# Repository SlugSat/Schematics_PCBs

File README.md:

# Schematics_PCBs
PCB Schematics for the whole team

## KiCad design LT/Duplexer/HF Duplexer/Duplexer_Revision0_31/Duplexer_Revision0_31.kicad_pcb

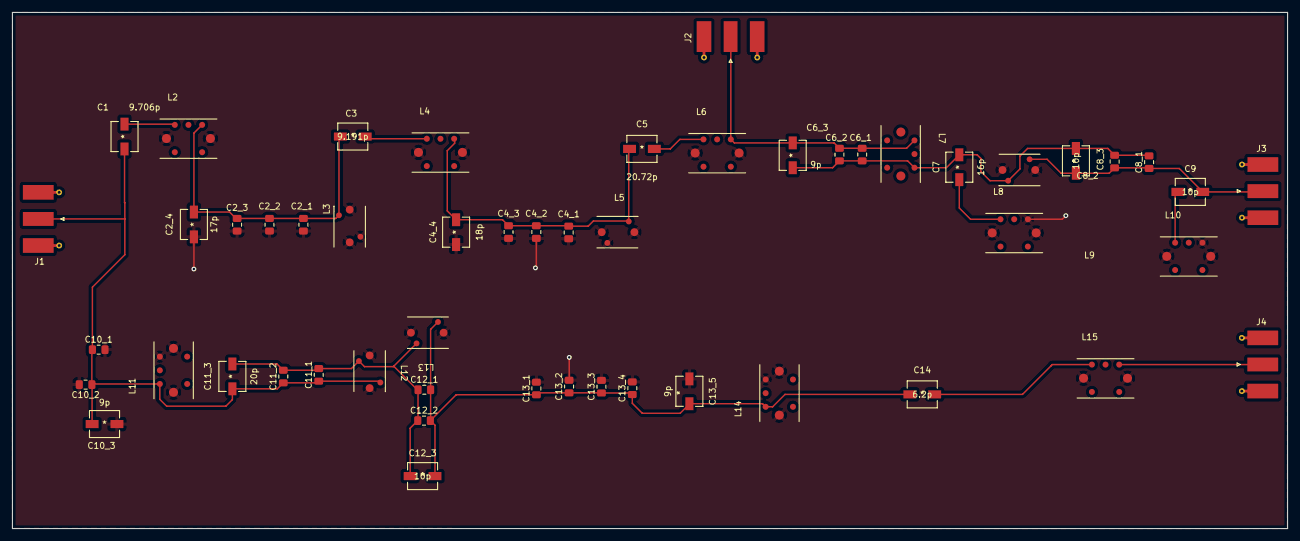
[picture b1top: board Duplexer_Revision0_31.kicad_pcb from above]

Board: 2 copper layers, 210.0 x 85.0 mm, 52 parts (0 on the bottom side), 16 nets.

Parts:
C1: 9.706p; GKG30086-05
C2_1, C13_1: 2.2n; C_0805_2012Metric_Pad1.18x1.45mm_HandSolder
C2_2, C4_2, C12_2: 100p; C_0805_2012Metric_Pad1.18x1.45mm_HandSolder
C2_3: 330p; C_0805_2012Metric_Pad1.18x1.45mm_HandSolder
C2_4: 17p; GKG30086-05
C3: 9.191p; GKG30086-05
C4_1, C10_1: 1.5n; C_0805_2012Metric_Pad1.18x1.45mm_HandSolder
C4_3, C8_1: 560p; C_0805_2012Metric_Pad1.18x1.45mm_HandSolder
C4_4: 18p; GKG30086-05
C5: 20.72p; GKG30086-05
C6_1, C13_2, C13_3: 1n; C_0805_2012Metric_Pad1.18x1.45mm_HandSolder
C6_2, C10_2, C13_4: 91p; C_0805_2012Metric_Pad1.18x1.45mm_HandSolder
C6_3, C10_3, C13_5: 9p; GKG30086-05
C7: 16p; GKG30086-05
C8_2: 180p; C_0805_2012Metric_Pad1.18x1.45mm_HandSolder
C8_3, C9, C12_3: 10p; GKG30086-05
C11_1, C12_1: 220p; C_0805_2012Metric_Pad1.18x1.45mm_HandSolder
C11_2: 30p; C_0805_2012Metric_Pad1.18x1.45mm_HandSolder
C11_3: 20p; GKG30086-05
C14: 6.2p; GKG30086-05
J1, J2, J3, J4: SMA_H_CONNECTOR; SMA_Molex_73251-1153_EdgeMount_Horizontal
L2: 5.827uH; 7M3_Shielded_Inductor_Series
L3: 22.44nH; 164_Shielded_Inductor_Series
L4: 6.2uH; 7M3_Shielded_Inductor_Series
L5: 26.73nH; 164_Shielded_Inductor_Series
L6: 2.895uH; 7M3_Shielded_Inductor_Series
L7: 27uH; 7M3_Shielded_Inductor_Series
L8: 1.8uH; 7M3_Shielded_Inductor_Series
L9: 39nH; 164_Shielded_Inductor_Series
L10: 3uH; 7M3_Shielded_Inductor_Series
L11: 18nH; 7M3_Shielded_Inductor_Series
L12: 91nH; 164_Shielded_Inductor_Series
L13: 110nH; 164_Shielded_Inductor_Series
L14: 6.8nH; 7M3_Shielded_Inductor_Series
L15: 4.7uH; 7M3_Shielded_Inductor_Series

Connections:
GND: C2_1.1, C2_2.1, C2_3.1, C2_4.1, C4_1.1, C4_2.1, C4_3.1, C4_4.1, C10_1.2, C10_2.2, C10_3.1, C13_1.2, C13_2.2, C13_3.2, C13_4.2, C13_5.1, L2.7 (GND), L2.8 (GND), L3.2 (GND), L3.3 (Finish), L3.4 (GND), L4.7 (GND), L4.8 (GND), L5.2 (GND), L5.3 (Finish), L5.4 (GND), L6.7 (GND), L6.8 (GND), L8.3 (Finish), L8.7 (GND), L8.8 (GND), L9.2 (GND), L9.4 (GND), L10.3 (Finish), L10.7 (GND), L10.8 (GND), L11.3 (Finish), L11.7 (GND), L11.8 (GND), L12.2 (GND), L12.4 (GND), L13.2 (GND), L13.4 (GND), L14.3 (Finish), L14.7 (GND), L14.8 (GND), L15.7 (GND), L15.8 (GND)
unnamed: C1.1, C10_1.1, C10_2.1, C10_3.2, C11_1.1, C11_2.1, C11_3.1, J1.1, L11.1 (Start), L12.1 (Start)
unnamed: C1.2, L2.1 (Start)
unnamed: C2_1.2, C2_2.2, C2_3.2, C2_4.2, C3.1, L2.3 (Finish), L3.1 (Start)
unnamed: C3.2, L4.1 (Start)
unnamed: C4_1.2, C4_2.2, C4_3.2, C4_4.2, C5.1, L4.3 (Finish), L5.1 (Start)
unnamed: C5.2, L6.1 (Start)
unnamed: C6_1.1, C6_2.1, C6_3.2, C7.2, C8_1.2, C8_2.2, C8_3.1, L7.3 (Finish), L9.1 (Start)
unnamed: C6_1.2, C6_2.2, C6_3.1, J2.1, L6.3 (Finish), L7.1 (Start)
unnamed: C7.1, L8.1 (Start)
unnamed: C8_1.1, C8_2.1, C8_3.2, C9.2, J3.1, L9.3 (Finish)
unnamed: C9.1, L10.1 (Start)
unnamed: C11_1.2, C11_2.2, C11_3.2, C12_1.1, C12_2.1, C12_3.1, L12.3 (Finish), L13.1 (Start)
unnamed: C12_1.2, C12_2.2, C12_3.2, C13_1.1, C13_2.1, C13_3.1, C13_4.1, C13_5.2, C14.1, L13.3 (Finish), L14.1 (Start)
unnamed: C14.2, L15.1 (Start)
unnamed: J4.1, L15.3 (Finish)

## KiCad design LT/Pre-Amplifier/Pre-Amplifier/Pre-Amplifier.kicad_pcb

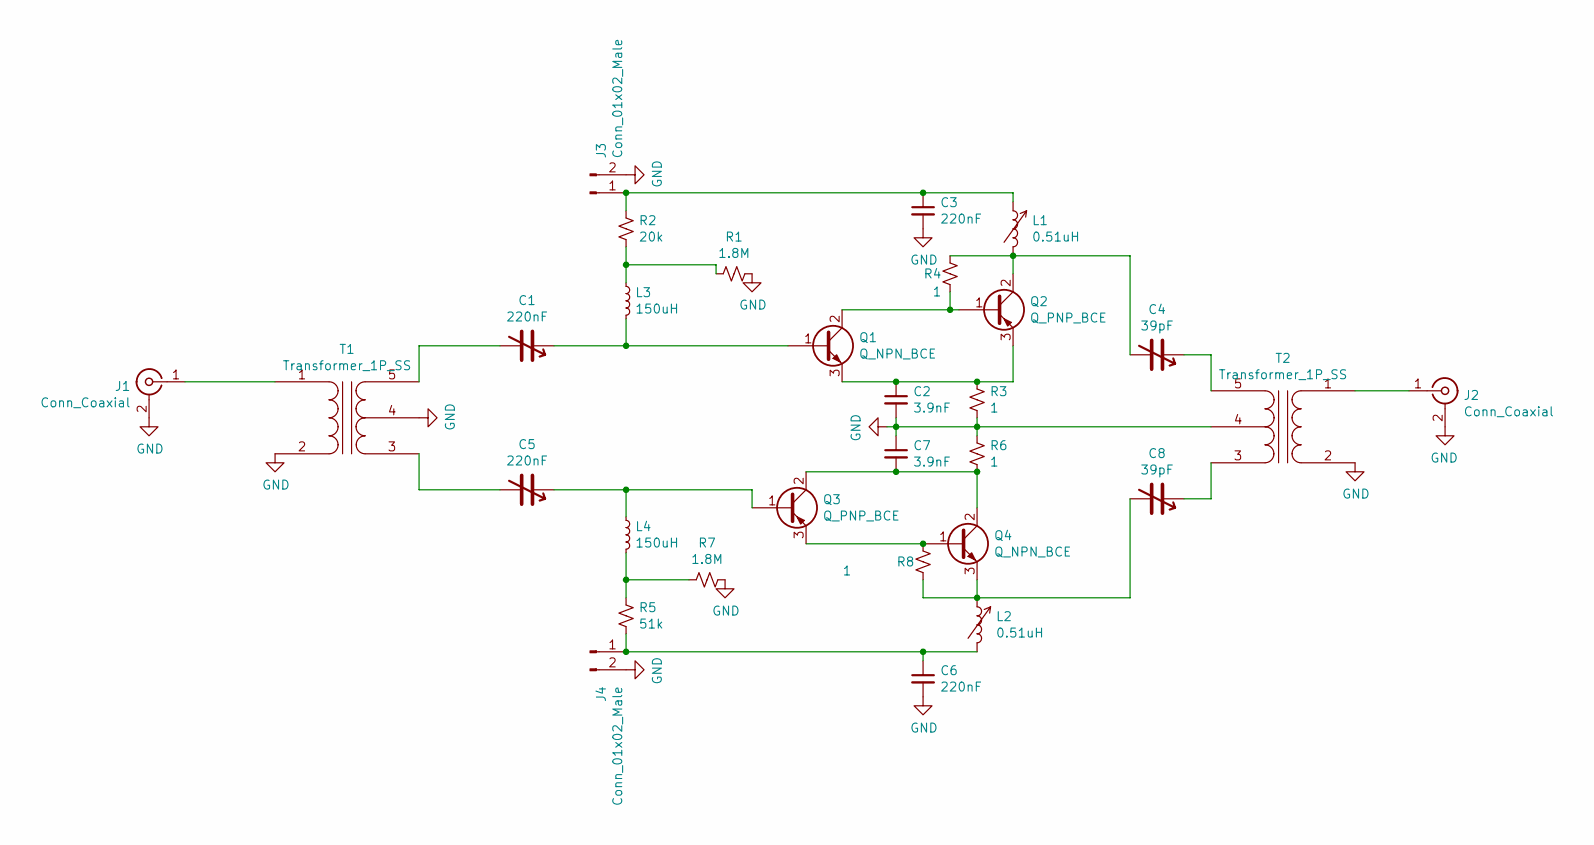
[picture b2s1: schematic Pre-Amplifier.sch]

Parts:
C1, C3, C5, C6: 220nF; C_0805_2012Metric_Pad1.18x1.45mm_HandSolder
C2, C7: 3.9nF; C_0805_2012Metric_Pad1.18x1.45mm_HandSolder
C4, C8: 39pF; C_0805_2012Metric_Pad1.18x1.45mm_HandSolder
J1, J2: Conn_Coaxial; SMA_Molex_73251-1153_EdgeMount_Horizontal
J3, J4: Conn_01x02_Male; PinHeader_1x02_P2.54mm_Vertical
L1, L2: 0.51uH; L_0805_2012Metric_Pad1.15x1.40mm_HandSolder
L3, L4: 150uH; L_0805_2012Metric_Pad1.15x1.40mm_HandSolder
Q1, Q4: Q_NPN_BCE; SOT-23_Handsoldering
Q2, Q3: Q_PNP_BCE; SOT-23_Handsoldering
R1, R7: 1.8M; R_0805_2012Metric_Pad1.20x1.40mm_HandSolder
R2: 20k; R_0805_2012Metric_Pad1.20x1.40mm_HandSolder
R3, R4, R6, R8: 1; R_0805_2012Metric_Pad1.20x1.40mm_HandSolder
R5: 51k; R_0805_2012Metric_Pad1.20x1.40mm_HandSolder
T1, T2: Transformer_1P_SS; Transformer_MACOM_SM-22

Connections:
GND: C2.2, C3.2, C6.2, C7.1, J1.2 (Ext), J2.2 (Ext), J3.2, J4.2, R1.2, R3.2, R6.1, R7.2, T1.2 (AB), T1.4 (SC), T2.2 (AB), T2.4 (SC)
unnamed: C1.1, L3.2, Q1.1 (B)
unnamed: C1.2, T1.5 (SB)
unnamed: C2.1, Q1.3 (E), Q2.3 (E), R3.1
unnamed: C3.1, J3.1, L1.1, R2.1
unnamed: C4.1, T2.5 (SB)
unnamed: C4.2, L1.2, Q2.2 (C), R4.1
unnamed: C5.1, L4.1, Q3.1 (B)
unnamed: C5.2, T1.3 (SA)
unnamed: C6.1, J4.1, L2.2, R5.2
unnamed: C7.2, Q3.2 (C), Q4.2 (C), R6.2
unnamed: C8.1, T2.3 (SA)
unnamed: C8.2, L2.1, Q4.3 (E), R8.2
unnamed: J1.1 (In), T1.1 (AA)
unnamed: J2.1 (In), T2.1 (AA)
unnamed: L3.1, R1.1, R2.2
unnamed: L4.2, R5.1, R7.1
unnamed: Q1.2 (C), Q2.1 (B), R4.2
unnamed: Q3.3 (E), Q4.1 (B), R8.1

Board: 2 copper layers, 30 parts (1 on the bottom side), 19 nets, no tracks yet.

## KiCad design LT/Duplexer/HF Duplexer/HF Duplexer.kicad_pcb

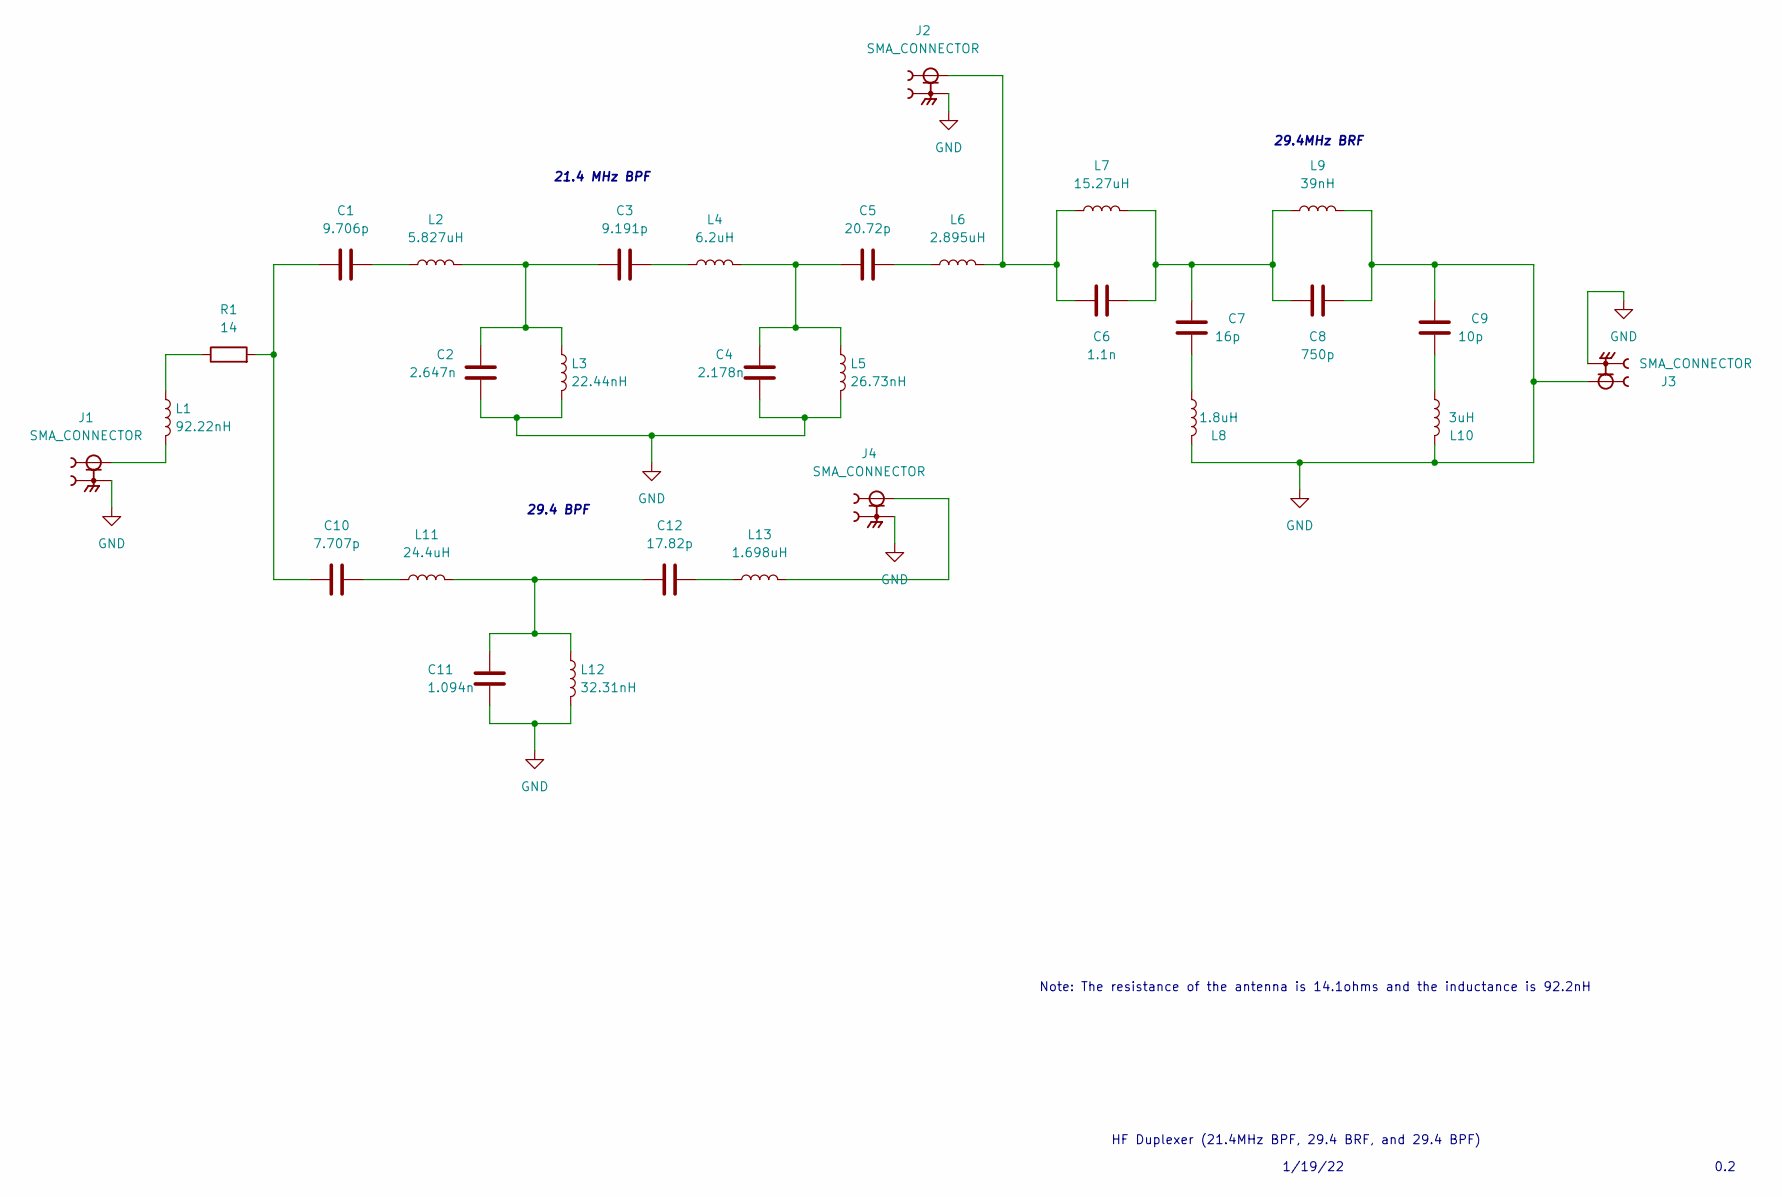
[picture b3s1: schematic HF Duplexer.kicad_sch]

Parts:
C1: 9.706p; C_0805_2012Metric_Pad1.18x1.45mm_HandSolder
C2: 2.647n; C_0805_2012Metric_Pad1.18x1.45mm_HandSolder
C3: 9.191p; C_0805_2012Metric_Pad1.18x1.45mm_HandSolder
C4: 2.178n; C_0805_2012Metric_Pad1.18x1.45mm_HandSolder
C5: 20.72p; C_0805_2012Metric_Pad1.18x1.45mm_HandSolder
C6: 1.1n; C_0805_2012Metric_Pad1.18x1.45mm_HandSolder
C7: 16p; C_0805_2012Metric_Pad1.18x1.45mm_HandSolder
C8: 750p; C_0805_2012Metric_Pad1.18x1.45mm_HandSolder
C9: 10p; C_0805_2012Metric_Pad1.18x1.45mm_HandSolder
C10: 7.707p; C_0805_2012Metric_Pad1.18x1.45mm_HandSolder
C11: 1.094n; C_0805_2012Metric_Pad1.18x1.45mm_HandSolder
C12: 17.82p; C_0805_2012Metric_Pad1.18x1.45mm_HandSolder
J1, J2, J3, J4: SMA_CONNECTOR; LPRS_SMA_CONNECTOR; PARTREV 1.3
L1: 92.22nH; L_0805_2012Metric_Pad1.15x1.40mm_HandSolder
L2: 5.827uH; L_0805_2012Metric_Pad1.15x1.40mm_HandSolder
L3: 22.44nH; L_0805_2012Metric_Pad1.15x1.40mm_HandSolder
L4: 6.2uH; L_0805_2012Metric_Pad1.15x1.40mm_HandSolder
L5: 26.73nH; L_0805_2012Metric_Pad1.15x1.40mm_HandSolder
L6: 2.895uH; L_0805_2012Metric_Pad1.15x1.40mm_HandSolder
L7: 15.27uH; L_0805_2012Metric_Pad1.15x1.40mm_HandSolder
L8: 1.8uH; L_0805_2012Metric_Pad1.15x1.40mm_HandSolder
L9: 39nH; L_0805_2012Metric_Pad1.15x1.40mm_HandSolder
L10: 3uH; L_0805_2012Metric_Pad1.15x1.40mm_HandSolder
L11: 24.4uH; L_0805_2012Metric_Pad1.15x1.40mm_HandSolder
L12: 32.31nH; L_0805_2012Metric_Pad1.15x1.40mm_HandSolder
L13: 1.698uH; L_0805_2012Metric_Pad1.15x1.40mm_HandSolder
R1: 14; R_0805_2012Metric_Pad1.20x1.40mm_HandSolder

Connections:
GND: C2.1, C4.1, C8.1, C9.1, C11.1, J1.G1, J1.G2, J1.G3, J1.G4, J2.G1, J2.G2, J2.G3, J2.G4, J3.1, J3.G1, J3.G2, J3.G3, J3.G4, J4.G1, J4.G2, J4.G3, J4.G4, L3.2, L5.2, L8.2, L9.2, L10.2, L12.2
unnamed: C1.1, C10.1, R1.2
unnamed: C1.2, L2.1
unnamed: C2.2, C3.1, L2.2, L3.1
unnamed: C3.2, L4.1
unnamed: C4.2, C5.1, L4.2, L5.1
unnamed: C5.2, L6.1
unnamed: C6.1, C7.1, C8.2, L7.2, L9.1
unnamed: C6.2, J2.1, L6.2, L7.1
unnamed: C7.2, L8.1
unnamed: C9.2, L10.1
unnamed: C10.2, L11.1
unnamed: C11.2, C12.1, L11.2, L12.1
unnamed: C12.2, L13.1
unnamed: J1.1, L1.2
unnamed: J4.1, L13.2
unnamed: L1.1, R1.1

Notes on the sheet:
29.4 BPF
21.4 MHz BPF
1/19/22
HF Duplexer (21.4MHz BPF, 29.4 BRF, and 29.4 BPF)
Note: The resistance of the antenna is 14.1ohms and the inductance is 92.2nH
0.2
29.4MHz BRF

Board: 2 copper layers, 30 parts (0 on the bottom side), 17 nets, no tracks yet.

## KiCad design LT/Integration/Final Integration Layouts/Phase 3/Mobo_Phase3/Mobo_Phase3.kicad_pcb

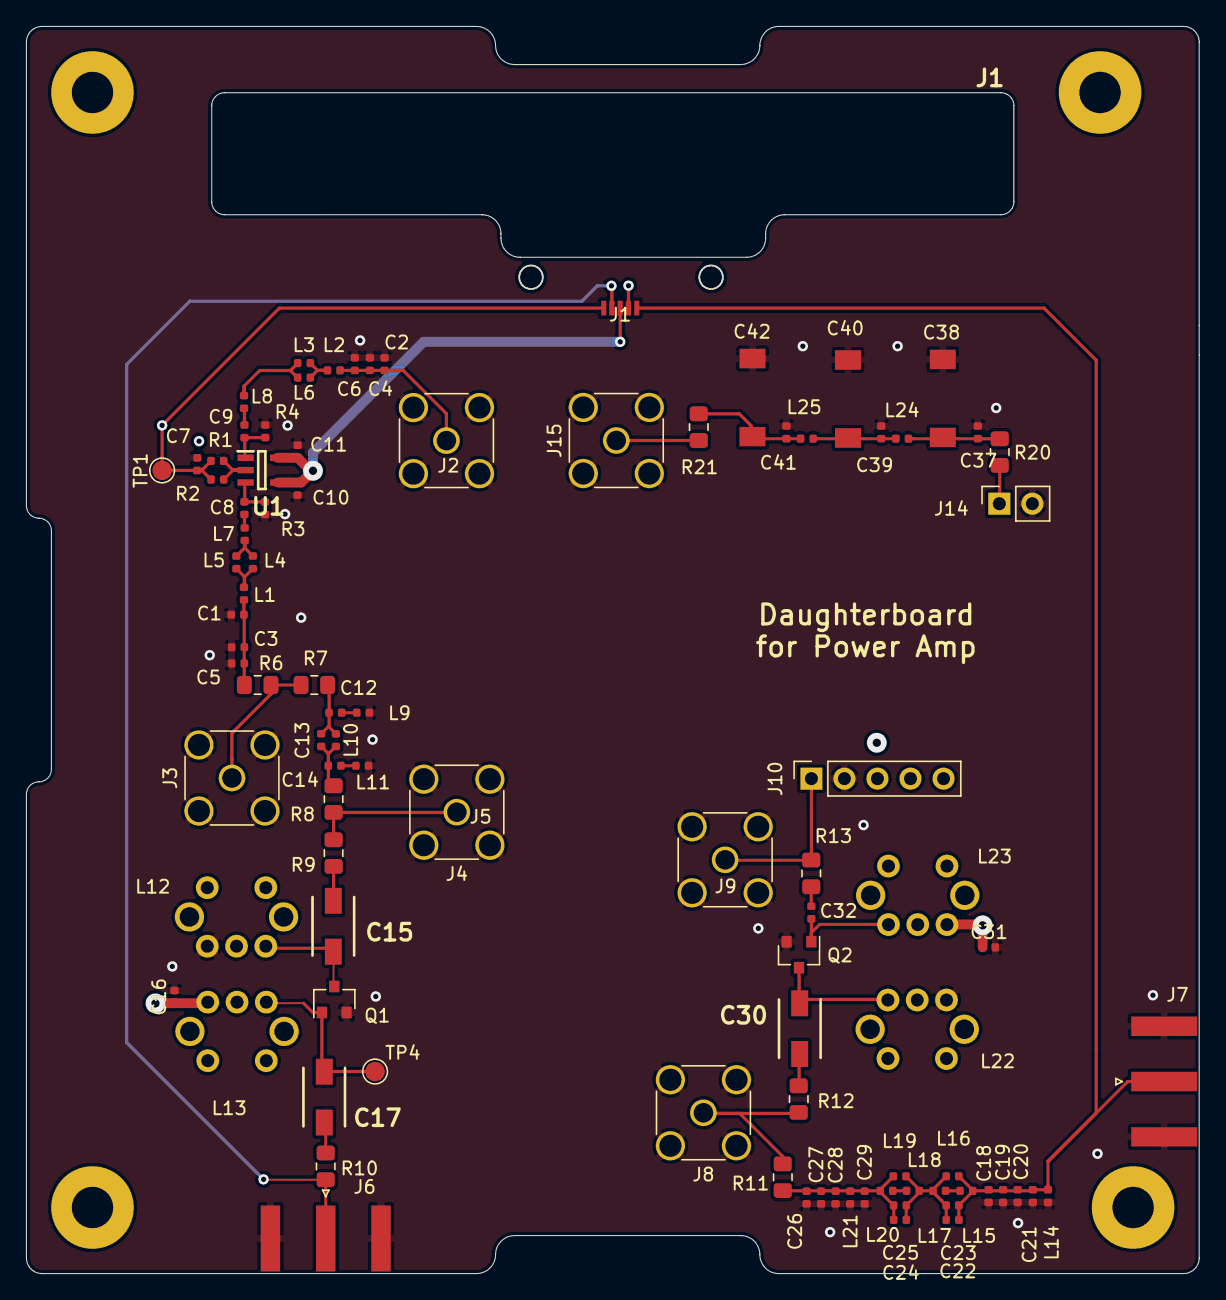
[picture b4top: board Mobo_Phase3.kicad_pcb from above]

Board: 4 copper layers, 90.2 x 95.9 mm, 94 parts (0 on the bottom side), 42 nets.

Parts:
C1, C2: 220pF; C_0402_1005Metric
C3, C4: 22pF; C_0402_1005Metric
C5, C6: 330pF; C_0402_1005Metric
C7: 10nH; C_0402_1005Metric
C8, C9, C10, C11: 10nF; C_0402_1005Metric
C12, C14: 27pF; C_0402_1005Metric
C13, C37, C41: 180pF; C_0402_1005Metric
C15, C17: 8-30pF; CAP_trimmer_SGC3_Download
C16, C31, C32: 1uF; C_0402_1005Metric
C18, C21, C23, C25, C28, C29: No Connect; C_0402_1005Metric
C19, C26: 560pF; C_0402_1005Metric
C20: 56 pF; C_0402_1005Metric
C22: 18pF; C_0402_1005Metric
C24: 43pF; C_0402_1005Metric
C27: 56pF; C_0402_1005Metric
C30: C_Variable; CAP_trimmer_SGC3_Download
C38, C40, C42: C_Variable; CAP_Trimmer_TZB4Z
C39: 270pF; C_0402_1005Metric
J1: Conn_01x05_Male; PCB_Single_Row_Connectors
J2, J3, J4, J8, J9, J15: Conn_Coaxial; SMA_Amphenol_132291_Vertical
J5: Conn_01x01_Male; STD_PCB_A2_v1.2_LT
J6, J7: Conn_Coaxial; SMA_Amphenol_132289_EdgeMount
J10: Conn_01x05_Female; PinSocket_1x05_P2.54mm_Vertical
J14: Conn_01x02_Female; PinSocket_1x02_P2.54mm_Vertical
L1, L2: 3.9nH; L_0402_1005Metric
L3, L4, L5, L6, L14, L21: 47nH; L_0402_1005Metric
L7, L8: 150nH; L_0402_1005Metric
L9, L11: 470nH; L_0402_1005Metric
L10: 82nH; L_0402_1005Metric
L12: 0.54-0.81uH; IND_trimmer_7M3
L13: 1.8-2.6uH; IND_trimmer_7M3
L15: 680nH; L_0402_1005Metric
L16, L19: No Connect; L_0402_1005Metric
L17: 6.8nH; L_0402_1005Metric
L18: 1.5uH; L_0402_1005Metric
L20: 72nH; L_0402_1005Metric
L22, L23: LTRIM; IND_trimmer_7M3
L24, L25: 330nH; L_0402_1005Metric
Q1, Q2: Q_NJFET_DSG; SOT-23
R1, R2: 120; R_0402_1005Metric
R3, R4: 330; R_0402_1005Metric
R6, R7, R8, R9, R10, R11, R12, R13, R20, R21: 0; R_0805_2012Metric_Pad1.15x1.40mm_HandSolder
TP1, TP4: TestPoint; TestPoint_Pad_D1.5mm
U1: BAP64Q

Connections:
+5V: C10.2, C11.1, J1.3, U1.4, U1.5
+8V: C16.1, C31.1, J1.2, L13.1, L23.1
/BPF-PRE_AMP: J8.1, R11.1, R12.2
/IMAGE_REJECT-LNA: J4.1, R8.1, R9.2
/Low Pass Filter/PA_OUT: J14.1, R20.2
/VA-IMAGE_REJECT: J3.1, R6.2, R7.2
/Variable Attenuator/Duplexer_Output: C2.1, C4.1, C6.1, J2.1, L2.2
Bus_64: C18.1, C19.1, C20.1, C21.1, C22.1, C23.1, J1.1, J7.1, L14.1, L15.1, L16.1
Bus_90: J1.4, J6.1, R10.1
Bus_116: C7.1, J1.5, R1.2, R2.2, TP1.1
GND: C1.2, C2.2, C3.2, C4.2, C5.2, C6.2, C7.2, C10.1, C11.2, C16.2, C18.2, C19.2, C20.2, C21.2, C26.2, C27.2, C28.2, C29.2, C31.2, C37.2, C38.2, C39.2, C40.2, C41.2, C42.2, J2.2, J3.2, J4.2, J6.2, J7.2, J8.2, J9.2, J10.2, J14.2, J15.2, L9.2, L11.2, L12.2, L14.2, L21.2, L22.2, Q1.2, Q2.2, R3.2, R4.2
unnamed: C1.1, C3.1, C5.1, L1.2, R6.1
unnamed: C8.1, R3.1, U1.3
unnamed: C8.2, L7.2
unnamed: C9.1, R4.1, U1.1
unnamed: C9.2, L8.2
unnamed: C12.1, C13.2, L10.1, R7.1
unnamed: C12.2, L9.1
unnamed: C13.1, C14.1, L10.2, R8.2
unnamed: C14.2, L11.1
unnamed: C15.1, L12.1, Q1.3
unnamed: C15.2, R9.1
unnamed: C17.1, R10.2
unnamed: C17.2, L13.2, Q1.1, TP4.1
unnamed: C22.2, C23.2, C24.2, C25.1, L16.2, L17.2, L18.1, L19.1
unnamed: C24.1, C25.2, C26.1, C27.1, C28.1, C29.1, L19.2, L20.2, L21.1, R11.2
unnamed: C30.1, L22.1, Q2.3
unnamed: C30.2, R12.1
unnamed: C32.1, R13.2
unnamed: C32.2, L23.2, Q2.1
unnamed: C37.1, C38.1, L24.1, R20.1
unnamed: C39.1, C40.1, L24.2, L25.1
unnamed: C41.1, C42.1, L25.2, R21.2
unnamed: J9.1, J10.1, R13.1
unnamed: J15.1, R21.1
unnamed: L1.1, L4.1, L5.1
unnamed: L2.1, L3.1, L6.1
unnamed: L3.2, L6.2, L8.1
unnamed: L4.2, L5.2, L7.1
unnamed: L15.2, L17.1
unnamed: L18.2, L20.1
unnamed: R1.1, R2.1, U1.2

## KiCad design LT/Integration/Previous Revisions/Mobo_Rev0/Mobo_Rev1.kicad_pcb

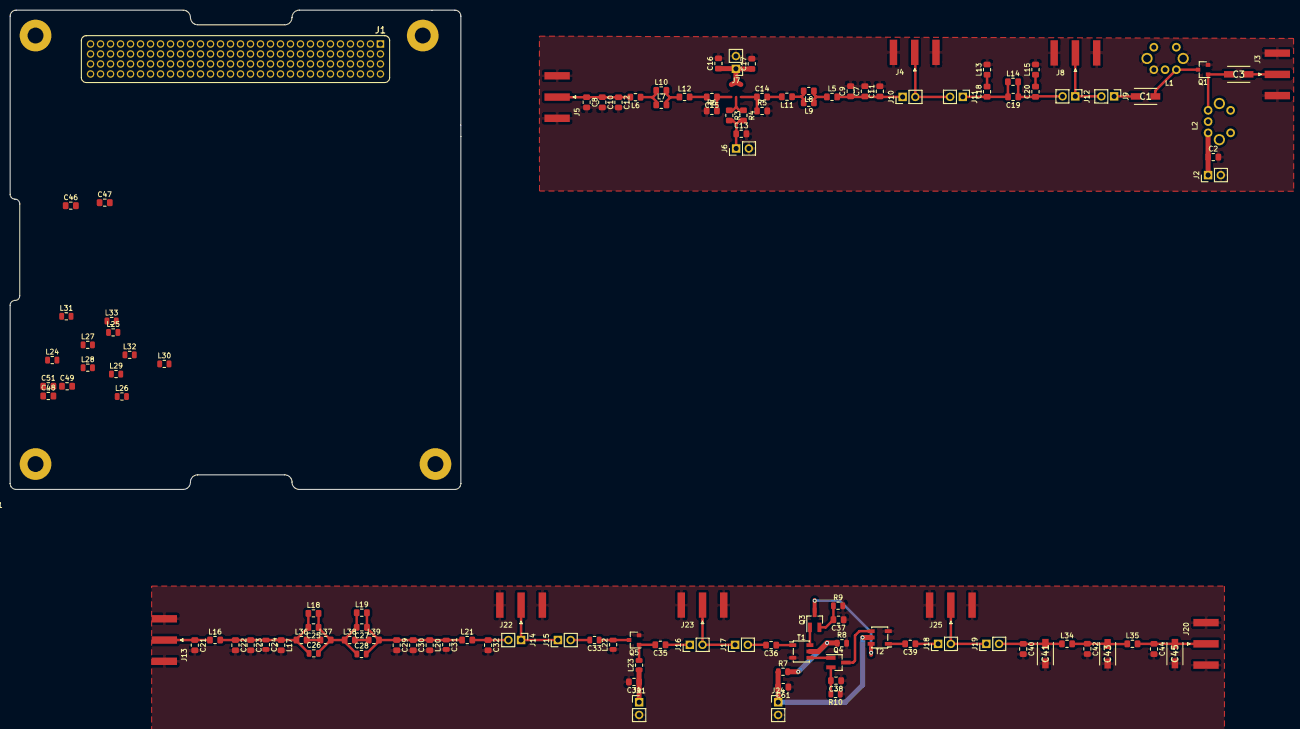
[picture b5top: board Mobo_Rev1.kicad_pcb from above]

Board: 2 copper layers, 90.2 x 95.9 mm, 124 parts (0 on the bottom side), 54 nets.

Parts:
C1, C3: 8-30pF; CAP_trimmer_SGC3_Download
C2, C34: 1uF; C_0805_2012Metric_Pad1.15x1.40mm_HandSolder
C7, C8: 220pF; C_0805_2012Metric_Pad1.15x1.40mm_HandSolder
C9, C10: 22pF; C_0805_2012Metric_Pad1.15x1.40mm_HandSolder
C11, C12: 330pF; C_0805_2012Metric_Pad1.15x1.40mm_HandSolder
C13: 10nH; C_0805_2012Metric_Pad1.15x1.40mm_HandSolder
C14, C15, C16, C17: 10nF; C_0805_2012Metric_Pad1.15x1.40mm_HandSolder
C18, C20: 27pF; C_0805_2012Metric_Pad1.15x1.40mm_HandSolder
C19: 180pF; C_0805_2012Metric_Pad1.15x1.40mm_HandSolder
C21, C32: No Connect; C_0805_2012Metric_Pad1.15x1.40mm_HandSolder
C22: 560p; C_0805_2012Metric_Pad1.15x1.40mm_HandSolder
C23, C30: 56pF; C_0805_2012Metric_Pad1.15x1.40mm_HandSolder
C24, C26, C28, C31: No Connect; C_0805_2012Metric
C25: 18pF; C_0805_2012Metric_Pad1.15x1.40mm_HandSolder
C27: 43pF; C_0805_2012Metric_Pad1.15x1.40mm_HandSolder
C29: 560pF; C_0805_2012Metric_Pad1.15x1.40mm_HandSolder
C33: C_Variable; C_0805_2012Metric
C35, C36, C39, C46, C47, C48, C49, C51: C; C_0805_2012Metric_Pad1.15x1.40mm_HandSolder
C37, C38, C61: 100n; C_0805_2012Metric_Pad1.15x1.40mm_HandSolder
C40, C44: 180p; C_0805_2012Metric_Pad1.15x1.40mm_HandSolder
C41, C43, C45: C_Variable; CAP_trimmer_SGC3_Download
C42: 270p; C_0805_2012Metric_Pad1.15x1.40mm_HandSolder
J1: Bus; STD_PCB_A1_v1.1
J2, J6, J7, J9, J10, J11, J12, J14, J15, J16, J17, J18, J19, J21, J24: Conn_01x02_Male; PinHeader_1x02_P2.54mm_Vertical
J3, J4, J5, J8, J13, J20: Conn_Coaxial; SMA_Amphenol_132289_EdgeMount
J22, J23, J25: Conn_01x02_Male; SMA_Amphenol_132289_EdgeMount
L1: 0.54-0.81uH; IND_trimmer_7M3
L2: 1.8-2.6uH; IND_trimmer_7M3
L5, L6: 3.9nH; L_0805_2012Metric_Pad1.15x1.40mm_HandSolder
L7, L8, L9, L10, L17, L20: 47nH; L_0805_2012Metric_Pad1.15x1.40mm_HandSolder
L11, L12: 150nH; L_0805_2012Metric_Pad1.15x1.40mm_HandSolder
L13, L15: 470nH; L_0805_2012Metric_Pad1.15x1.40mm_HandSolder
L14: 82nH; L_0805_2012Metric_Pad1.15x1.40mm_HandSolder
L16, L21: Shorted Connection; L_0805_2012Metric_Pad1.15x1.40mm_HandSolder
L18, L19: No Connect; L_0805_2012Metric_Pad1.15x1.40mm_HandSolder
L22: LTRIM; L_0805_2012Metric
L23: 1.8-2.6uH; L_0805_2012Metric
L24, L25, L26, L27, L28, L29, L30, L31, L32, L33: L; L_0805_2012Metric
L34, L35: 330n; L_0805_2012Metric_Pad1.15x1.40mm_HandSolder
L36: 680nH; L_0805_2012Metric_Pad1.15x1.40mm_HandSolder
L37: 6.8nH; L_0805_2012Metric_Pad1.15x1.40mm_HandSolder
L38: 1.5uH; L_0805_2012Metric_Pad1.15x1.40mm_HandSolder
L39: 72nH; L_0805_2012Metric_Pad1.15x1.40mm_HandSolder
Q1: 2N5486; SOT-23
Q3: Q_NPN_BEC; SOT-23_Handsoldering
Q4: Q_PNP_BEC; SOT-23_Handsoldering
Q5: Q_NJFET_DSG; SOT-23
R3, R4: 120; R_0805_2012Metric_Pad1.15x1.40mm_HandSolder
R5, R6: 330; R_0805_2012Metric_Pad1.15x1.40mm_HandSolder
R7: 33k; C_0805_2012Metric
R8: 47k; C_0805_2012Metric
R9, R10: 470; C_0805_2012Metric
T1, T2: TC2-1T+; Transformer_MACOM_SM-22

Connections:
+5V: C16.1, C17.1, J7.1
+8V: C2.1, C34.1, J2.1, J21.1, L2.1, L23.1
/29.4 MHz Bandpass Filter/29.4BPF_OUT: J14.1, J22.1
/Image Reject Filter/Image_Reject_Out: J8.1, J12.1
/LNA/LNAout: C3.1, J3.1
/Power Amplifier/PA_OUT: J18.2, J25.1
/Pre Amplifier/PREAMP_OUT: J16.2, J23.1
/Variable Attenuator/Variable_Attenuator_Out: J4.1, J10.2
GND: C2.2, C7.2, C8.2, C9.2, C10.2, C11.2, C12.2, C13.2, C16.2, C17.2, C21.2, C22.2, C23.2, C24.2, C29.2, C30.2, C31.2, C32.2, C34.2, C37.1, C38.1, C40.2, C41.2, C42.2, C43.2, C44.2, C45.2, C61.1, J2.2, J3.2, J4.2, J5.2, J6.2, J7.2, J8.2, J13.2, J20.2, J21.2, J22.2, J23.2, J24.2, J25.2, L1.2, L13.2, L15.2, L17.2, L20.2, L22.1, Q1.3, Q5.2, R5.2, R6.1, R8.2, R9.2, R10.1, T1.2, T2.2
unnamed: C1.1, L1.1, Q1.2
unnamed: C1.2, J9.1
unnamed: C3.2, L2.2, Q1.1
unnamed: C8.1, C10.1, C12.1, J5.1, L6.2
unnamed: C7.1, C9.1, C11.1, J10.1, L5.2
unnamed: C13.1, J6.1, R3.2, R4.2
unnamed: C14.1, R5.1
unnamed: C14.2, L11.2
unnamed: C15.1, R6.2
unnamed: C15.2, L12.2
unnamed: C18.1, C19.2, J11.1, L14.1
unnamed: C18.2, L13.1
unnamed: C19.1, C20.1, J12.2, L14.2
unnamed: C20.2, L15.1
unnamed: C21.1, J13.1, L16.1
unnamed: C22.1, C23.1, C24.1, C25.2, C26.1, L16.2, L17.1, L18.1, L36.1
unnamed: C25.1, C26.2, C27.2, C28.1, L18.2, L19.1, L37.2, L38.1
unnamed: C27.1, C28.2, C29.1, C30.1, C31.1, L19.2, L20.1, L21.1, L39.2
unnamed: C32.1, J14.2, L21.2
unnamed: C33.1, L22.2, Q5.3
unnamed: C33.2, J15.2
unnamed: C35.1, J16.1
unnamed: C35.2, L23.2, Q5.1
unnamed: C36.1, T1.1
unnamed: C36.2, J17.2
unnamed: C37.2, Q3.2, R9.1
unnamed: C38.2, Q4.2, R10.2
unnamed: C39.1, J18.1
unnamed: C39.2, T2.1
unnamed: C40.1, C41.1, J19.2, L34.1
unnamed: C42.1, C43.1, L34.2, L35.1
unnamed: C44.1, C45.1, J20.1, L35.2
unnamed: C61.2, J24.1, R7.1, T2.4
unnamed: L5.1, L8.1, L9.1
unnamed: L6.1, L7.1, L10.1
unnamed: L7.2, L10.2, L12.1
unnamed: L8.2, L9.2, L11.1
unnamed: L36.2, L37.1
unnamed: L38.2, L39.1
unnamed: Q3.1, T1.5
unnamed: Q3.3, T2.5
unnamed: Q4.1, T1.3
unnamed: Q4.3, T2.3
unnamed: R3.1, R4.1
unnamed: R7.2, R8.1, T1.4

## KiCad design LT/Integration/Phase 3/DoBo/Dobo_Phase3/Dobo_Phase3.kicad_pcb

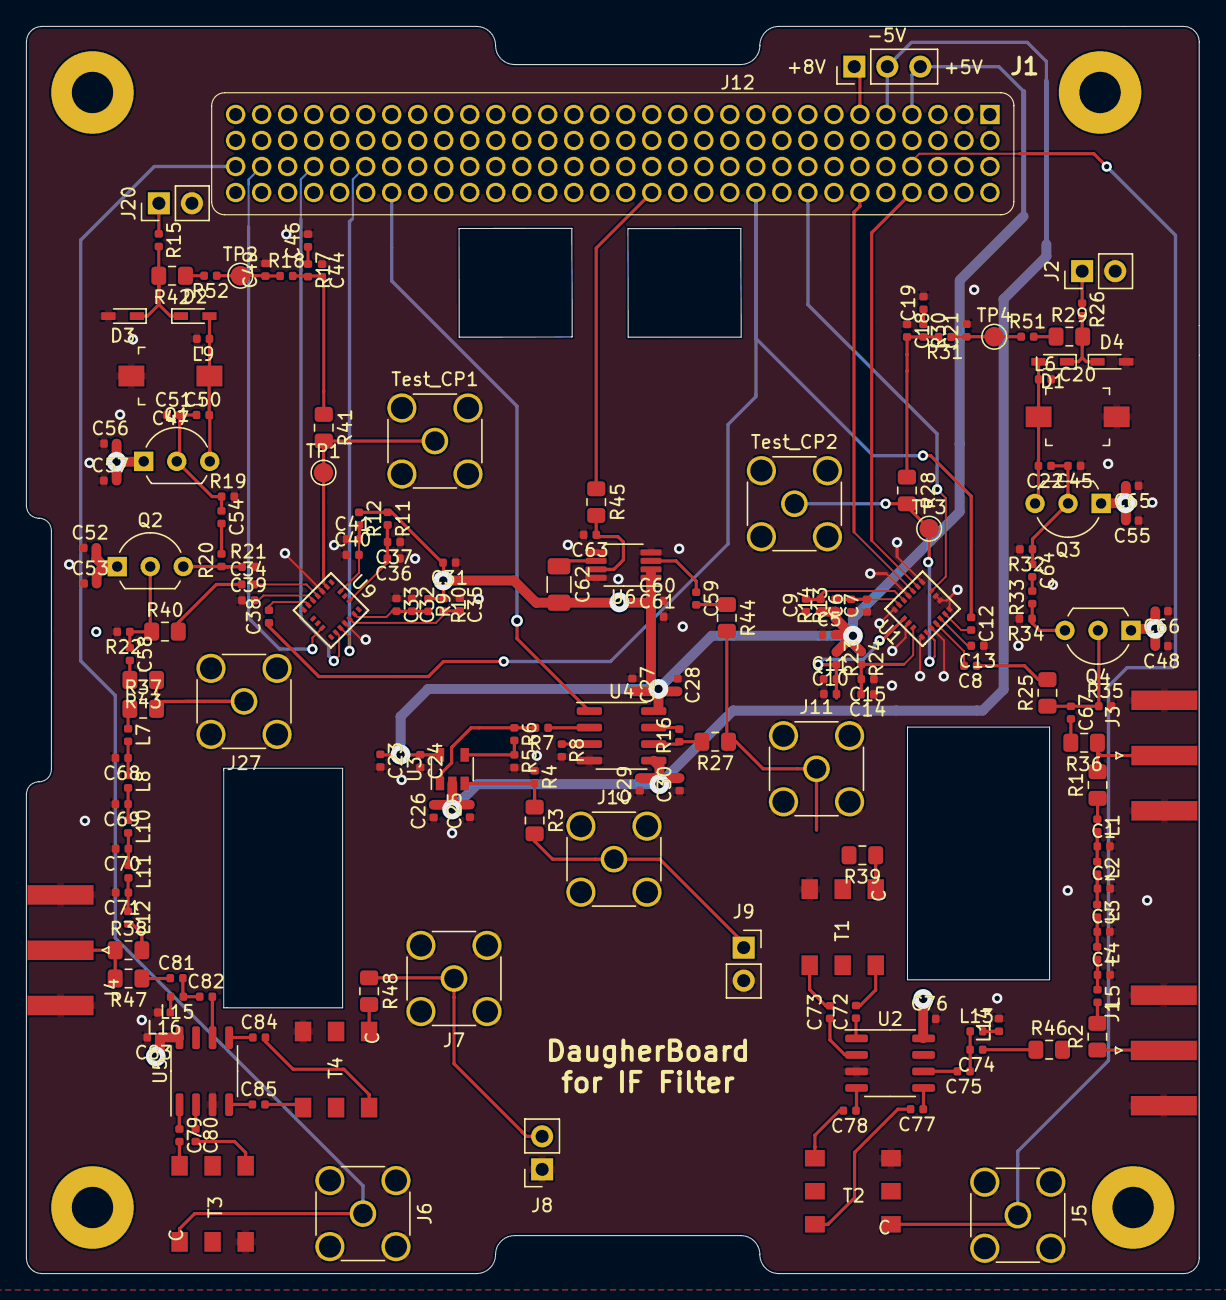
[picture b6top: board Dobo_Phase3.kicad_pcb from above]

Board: 4 copper layers, 90.2 x 95.9 mm, 187 parts (0 on the bottom side), 113 nets.

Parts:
C1: 91pF; C_0402_1005Metric
C2, C3, C4: 160pF; C_0402_1005Metric
C5, C6, C9, C10, C13, C14, C31, C32, C35, C36, C39, C40, C53, C55, C57, C58, C66, C67: 100nF; C_0402_1005Metric
C7, C11, C15, C33, C37, C41, C48, C52, C56, C61, C63, C65: 100pF; C_0402_1005Metric
C8, C12, C34, C38: 1000pF; C_0402_1005Metric
C18, C44: 12nF; C_0402_1005Metric
C19, C46: 80nF; C_0402_1005Metric
C20, C47: SGC35060; C_Trimmer_Murata_TZB4-B
C21, C49: 220nF; C_0402_1005Metric
C22, C50: 22pF; C_0402_1005Metric
C23, C25: 4.7uF; C_0402_1005Metric
C24, C26: 10nF; C_0402_1005Metric
C27, C29, C59, C60: 0.1uH; C_0402_1005Metric
C28, C30: 6.8uH; C_0402_1005Metric
C45, C51: 47pF; C_0402_1005Metric
C54, C64: 10pF; C_0402_1005Metric
C62: 100uH; C_1206_3216Metric
C68, C71: 120pF; C_0402_1005Metric
C69, C70: 200pF; C_0402_1005Metric
C72, C73, C75, C76, C77, C78, C79, C80, C82, C83, C84, C85: 10u; C_0402_1005Metric
C74, C81: 2.2n; C_0402_1005Metric
D1, D2, D3, D4: 1SV304; D_SC-80_HandSoldering
J1, J3, J4: Conn_Coaxial; SMA_Amphenol_132289_EdgeMount
J2, J20: Conn_01x02_Male; PinHeader_1x02_P2.54mm_Vertical
J5, J6, J7, J10, J11, J27: Conn_Coaxial; SMA_Amphenol_132291_Vertical
J8, J9: Conn_01x02_Female; PinSocket_1x02_P2.54mm_Vertical
J12: Conn_01x03_Male; PinHeader_1x03_P2.54mm_Vertical
J46: Bus; STD_PCB_A1_v1.1
L1, L5: shorted; L_0402_1005Metric
L2, L4: 270nH; L_0402_1005Metric
L3: 330nH; L_0402_1005Metric
L6, L9: 680nH; L_0402_1005Metric
L7, L12: Matching; L_0402_1005Metric
L8: 360nH; L_0402_1005Metric
L10: 390pF; L_0402_1005Metric
L11: 360pF; L_0402_1005Metric
L13, L15: 5.6u; L_0402_1005Metric
L14, L16: 680n; L_0402_1005Metric
Q1, Q2, Q3, Q4: 2N5486 JFET; TO-92L_Inline_Wide
R1, R2, R3, R25, R27, R28, R29, R36, R37, R38, R39, R40, R41, R42, R43, R44, R45, R46, R47, R48: 0; R_0805_2012Metric_Pad1.15x1.40mm_HandSolder
R4, R5: 50; R_0402_1005Metric
R6, R16: 1000; R_0402_1005Metric
R7, R8: 29.4; R_0402_1005Metric
R9, R11, R12, R13, R23, R24: 18; R_0402_1005Metric
R10, R14, R15, R26, R51, R52: 10k; R_0402_1005Metric
R17, R30: 62k; R_0402_1005Metric
R18, R19, R22, R31, R32, R35: 1k; R_0402_1005Metric
R20, R33: 1 Ohm; R_0402_1005Metric
R21, R34: 100k; R_0402_1005Metric
T1, T2, T3, T4: Transformer_6; PWB1040L
TP1, TP2, TP3, TP4: TestPoint; TestPoint_Pad_D1.5mm
Test_CP1, Test_CP2: Conn_Coaxial; SMA_Amphenol_132291_Vertical
U1, U9: LMX231X
U2, U5: SA602; SO-8_3.9x4.9mm_P1.27mm
U3: LMH6624; SOT-23-5
U4: LMH6505; SOIC-8_3.9x4.9mm_P1.27mm
U6: AD8361; MSOP-8_3x3mm_P0.65mm

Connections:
+5V: C5.2, C23.1, C24.1, C27.2, C28.2, C31.2, C60.1, C61.1, C62.2, J12.3, J46.4, R9.1, R10.1, R11.1, R12.1, R13.1, R14.1, R23.1, R24.1, U3.5, U4.8, U6.1, U6.2
+8V: C48.2, C52.2, C53.2, C55.2, C56.2, C57.2, C65.2, C66.2, C76.1, C83.1, J12.1, J46.6, Q1.1, Q2.1, Q3.1, Q4.1, U2.8, U5.8
-5V: C25.2, C26.2, C29.2, C30.2, J12.2, J46.5, U3.2, U4.5
/Down_Mixer-IF_Filter: J7.1, J8.2, R48.1
/IF_Filter-VGA: J9.1, J10.1, R3.2
/LPF-Down_Mixer: J4.1, R38.1, R47.2
/Low Pass Filter for 10m PLL/Local_Oscillator_Output: J1.1, R2.1
/PLL_10m_LPF: J3.1, R1.2, R36.1
/PLL_15m-LPF: J27.1, R37.2, R43.1
/VGA-Detector: J11.1, R27.1, R44.2
Bus_64: J5.1, J46.64, T2.1
Bus_85: J46.85, U9.13
Bus_87: J46.87, U9.12
Bus_89: J46.89, U9.10
Bus_90: J6.1, J46.90, T3.1
Bus_94: J46.94, U1.12
Bus_96: J46.96, U1.13
Bus_99: J46.98, U1.10
Bus_100: C12.1, C38.1, J46.100
Bus_104: J46.104, R45.1
Bus_114: J46.114, U4.1
CE: C35.2, R10.2, U9.15
CE_2: C9.2, R14.2, U1.15
CPo: R41.2, TP1.1, Test_CP1.1, U9.2
CPo_2: R28.2, TP3.1, Test_CP2.1, U1.2
F_IN: C34.2, U9.4
F_IN_2: C8.2, U1.4
GND: C1.2, C2.2, C3.2, C4.2, C5.1, C6.1, C7.1, C9.1, C10.1, C11.1, C13.1, C14.1, C15.1, C18.1, C19.2, C20.2, C21.2, C23.2, C24.2, C25.1, C26.1, C27.1, C28.1, C29.1, C30.1, C31.1, C32.1, C33.1, C35.1, C36.1, C37.1, C39.1, C40.1, C41.1, C44.1, C45.1, C46.2, C47.2, C48.1, C49.2, C51.1, C52.1, C53.1, C55.1, C56.1, C57.1, C60.2, C61.2, C63.2, C65.1, C66.1, C68.2, C69.2, C70.2, C71.2, C76.2, C83.2, D3.2, D4.2, J1.2, J2.2, J3.2, J4.2, J5.2, J6.2, J7.2, J8.1, J9.2, J10.2, J11.2, J20.2, J27.2, J46.2, L6.2, L9.2, L14.2, L16.2, R4.1, R5.2, R8.2, R19.2, R21.2, R22.2, R32.2, R34.2, R35.2, T1.3, T2.3, T3.3, T4.3, Test_CP1.2, Test_CP2.2, U1.1, U1.3, U1.7, U1.8, U1.9, U1.11, U1.14, U1.17, U1.19, U2.3, U4.4, U5.3, U6.4, U6.5, U6.8, U9.3, U9.14
unnamed: C1.1, L1.2, L2.1
unnamed: C2.1, L2.2, L3.1
unnamed: C3.1, L3.2, L4.1
unnamed: C4.1, L4.2, L5.1
unnamed: C8.1, R25.2
unnamed: C12.2, U1.6
unnamed: C13.2, U1.5
unnamed: C18.2, R28.1, R30.2, R31.2
unnamed: C19.1, R30.1
unnamed: C20.1, C22.2, D1.2, L6.1, Q3.3
unnamed: C21.1, R31.1, R51.1, TP4.1
unnamed: C22.1, C45.2, C64.1, Q3.2, R32.1
unnamed: C34.1, R40.2
unnamed: C38.2, U9.6
unnamed: C39.2, U9.5
unnamed: C44.2, R17.2, R18.2, R41.1
unnamed: C46.1, R17.1
unnamed: C47.1, C50.2, D2.2, L9.1, Q1.3
unnamed: C49.1, R18.1, R52.1, TP2.1
unnamed: C50.1, C51.2, C54.1, Q1.2, R19.1
unnamed: C54.2, R20.2
unnamed: C58.1, Q2.2, R22.1, R40.1
unnamed: C58.2, R43.2
unnamed: C59.1, U6.3
unnamed: C59.2, R44.1
unnamed: C62.1, U6.6
unnamed: C63.1, R45.2, U6.7
unnamed: C64.2, R33.2
unnamed: C67.1, Q4.2, R25.1, R35.1
unnamed: C67.2, R36.2
unnamed: C68.1, L7.2, L8.1
unnamed: C69.1, L8.2, L10.1
unnamed: C70.1, L10.2, L11.1
unnamed: C71.1, L11.2, L12.1
unnamed: C72.1, U2.1
unnamed: C72.2, T1.6
unnamed: C73.1, U2.2
unnamed: C73.2, T1.4
unnamed: C74.1, R46.1
unnamed: C74.2, C75.1, L13.1
unnamed: C75.2, U2.6
unnamed: C77.1, U2.5
unnamed: C77.2, T2.6
unnamed: C78.1, U2.4
unnamed: C78.2, T2.4
unnamed: C79.1, U5.1
unnamed: C79.2, T3.6
unnamed: C80.1, U5.2
unnamed: C80.2, T3.4
unnamed: C81.1, R47.1
unnamed: C81.2, C82.1, L15.1
unnamed: C82.2, U5.6
unnamed: C84.1, U5.5
unnamed: C84.2, T4.6
unnamed: C85.1, U5.4
unnamed: C85.2, T4.4
unnamed: D1.1, D4.1, R26.2, R29.2
unnamed: D2.1, D3.1, R15.2, R42.2
unnamed: J2.1, R26.1
unnamed: J20.1, R15.1
unnamed: L1.1, R1.1
unnamed: L5.2, R2.2
unnamed: L7.1, R37.1
unnamed: L12.2, R38.2
unnamed: L13.2, L14.1
unnamed: L15.2, L16.1
unnamed: Q2.3, R20.1, R21.1
unnamed: Q4.3, R33.1, R34.1
unnamed: R3.1, R4.2, U3.3
unnamed: R5.1, R6.2, U3.4
unnamed: R6.1, R7.2, U3.1
unnamed: R7.1, U4.2
unnamed: R8.1, U4.3
unnamed: R16.1, R27.2, U4.6
unnamed: R16.2, U4.7
unnamed: R29.1, R51.2
unnamed: R39.1, T1.1
unnamed: R42.1, R52.2
unnamed: R48.2, T4.1
V_uC: C32.2, C33.2, R9.2, U9.16
V_uC_2: C6.2, C7.2, R13.2, U1.16
Vcc: C36.2, C37.2, R11.2, U9.18
Vcc_2: C10.2, C11.2, R23.2, U1.18
Vp: C40.2, C41.2, R12.2, U9.20
Vp_2: C14.2, C15.2, R24.2, U1.20

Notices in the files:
parts and their libraries:
Copyright 2021 Accelerated Designs. All rights reserved.
